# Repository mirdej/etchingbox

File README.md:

# AETZBOX
### DIY Mobile PCB Etching KIT

## The Idea 
Build a portable / mobile PCB etching workstation that fulfills these criteria
* waterproof
* able to etch 100x160mm double sided boards with 8mil precision
* low cost.  total bill of materials should not exceed 150 CHF
* diy approach, mostly laser cut plexi and easily sourceable materials
* fits in a RAKO Box

Some guiding ideas
* use very little but always fresh chemicals 
* good heat management: etching has to be done at 45-50 degrees celsius, developer has to be kept at >20 degrees as well (in my workshop, temperatures can easily drop below 16 degrees and developing is a pain).
* all material and chemicals travel in the box. liquid waste can travel in the box as well until it can properly disposed of.
* should be easy to clean. no electronics exposed to moisture. 
* as few as possible switches and electrical contacts exposed to the harsh etching environment
* self illuminating

## More Info
https://wiki.sgmk-ssam.ch/index.php/EtchingBox

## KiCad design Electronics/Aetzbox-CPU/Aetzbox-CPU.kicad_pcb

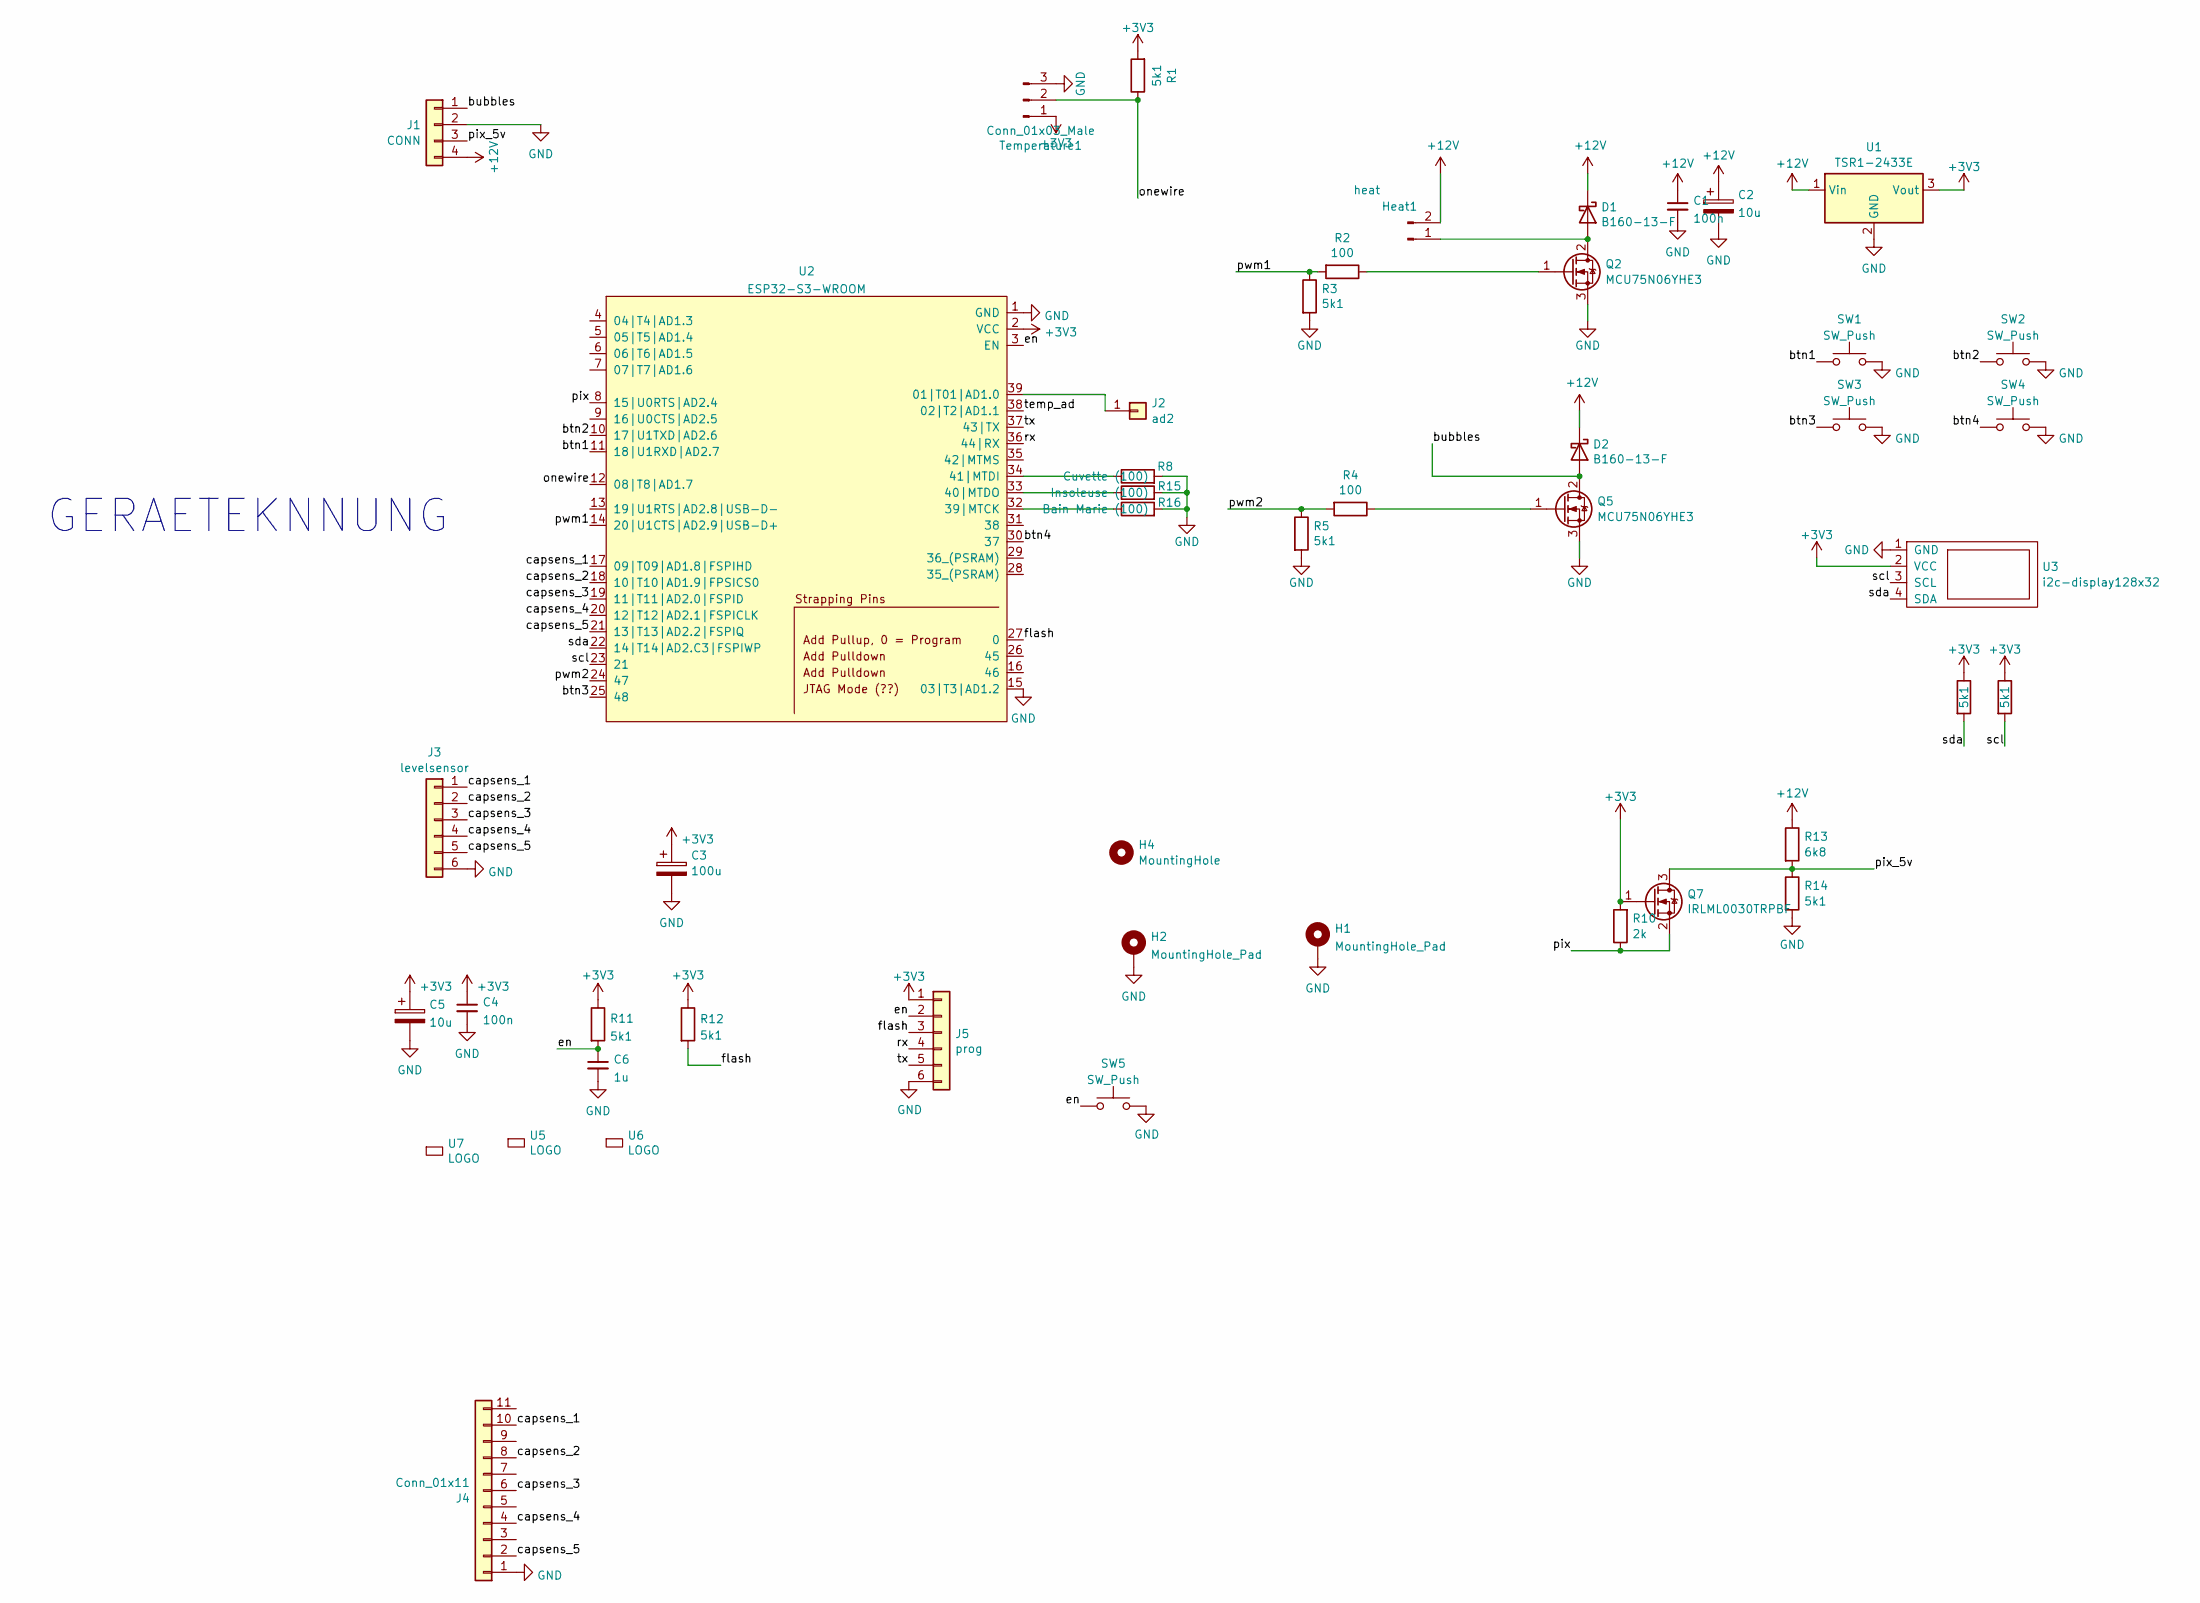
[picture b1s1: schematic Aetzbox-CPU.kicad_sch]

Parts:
C1, C4: 100n; C_0603_1608Metric_Pad1.05x0.95mm_HandSolder
C2, C5: 10u; C_1206_3216Metric_Pad1.42x1.75mm_HandSolder
C3: 100u; CP_EIA-6032-20_AVX-F
C6: 1u; C_0603_1608Metric_Pad1.05x0.95mm_HandSolder
D1, D2: B160-13-F; D_SMA-SMB_Universal_Handsoldering
H1, H2: MountingHole_Pad; MountingHole_2.5mm_Pad
H4: MountingHole; MountingHole_2.5mm
Heat1: heat; Molex_Mini-Fit_Jr_5566-02A_2x01_P4.20mm_Vertical
J1: CONN; Molex_Mini-Fit_Jr_5569-04A2_2x02_P4.20mm_H+V
J2: ad2; Solderpad_1mm
J3: levelsensor; PinSocket_1x06_P1.27mm_Vertical
J4: Conn_01x11; Molex_200528-0100_1x10-1MP_P1.00mm_Horizontal
J5: prog; ESP-POGO-PROG-THT
Q2, Q5: MCU75N06YHE3; TO-252-2
Q7: IRLML0030TRPBF; SOT-23
R1, R3, R5, R6, R7, R11, R12, R14: 5k1; R_0805_2012Metric
R2, R4: 100; R_0805_2012Metric
R8: Cuvette (100); R_0805_2012Metric
R10: 2k; R_0805_2012Metric
R13: 6k8; R_0805_2012Metric
R15: Insoleuse (100); R_0805_2012Metric
R16: Bain Marie (100); R_0805_2012Metric
SW1, SW2, SW3, SW4: SW_Push; Alps_Tactile_Switch
SW5: SW_Push; MiniButtonPLCC4
Temperature1: Conn_01x03_Male; Molex_KK-254_AE-6410-03A_1x03_P2.54mm_Vertical
U1: TSR1-2433E; Converter_DCDC_TRACO_TSR1-xxxxE_THT
U2: ESP32-S3-WROOM
U3: i2c-display128x32; Bangood_I2C_Display
U5: LOGO; logo_anyma_tiny
U6: LOGO; logo_sgmk
U7: LOGO; OSHW-Logo2_7.3x6mm_SilkScreen

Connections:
+3V3: C3.1, C4.1, C5.1, J5.1, Q7.1 (G), R1.2, R6.1, R7.1, R10.2, R11.1, R12.1, Temperature1.1, U1.3 (Vout), U2.2 (VCC), U3.2 (VCC)
+12V: C1.1, C2.1, D1.1 (K), D2.1 (K), Heat1.2, J1.4, R13.1, U1.1 (Vin)
/btn1: SW1.1, U2.11 (18|U1RXD|AD2.7)
/btn2: SW2.1, U2.10 (17|U1TXD|AD2.6)
/btn3: SW3.1, U2.25 (48)
/btn4: SW4.1, U2.30 (37)
/bubbles: D2.2 (A), J1.1, Q5.2 (D)
/capsens_1: J3.1, J4.10, U2.17 (09|T09|AD1.8|FSPIHD)
/capsens_2: J3.2, J4.8, U2.18 (10|T10|AD1.9|FPSICS0)
/capsens_3: J3.3, J4.6, U2.19 (11|T11|AD2.0|FSPID)
/capsens_4: J3.4, J4.4, U2.20 (12|T12|AD2.1|FSPICLK)
/capsens_5: J3.5, J4.2, U2.21 (13|T13|AD2.2|FSPIQ)
/en: C6.1, J5.2, R11.2, SW5.2, U2.3 (EN)
/flash: J5.3, R12.2, U2.27 (0)
/onewire: R1.1, Temperature1.2, U2.12 (08|T8|AD1.7)
/pix: Q7.2 (S), R10.1, U2.8 (15|U0RTS|AD2.4)
/pix_5v: J1.3, Q7.3 (D), R13.2, R14.1
/pwm1: R2.2, R3.1, U2.14 (20|U1CTS|AD2.9|USB-D+)
/pwm2: R4.2, R5.1, U2.24 (47)
/rx: J5.4, U2.36 (44|RX)
/scl: R7.2, U2.23 (21), U3.3 (SCL)
/sda: R6.2, U2.22 (14|T14|AD2.C3|FSPIWP), U3.4 (SDA)
/temp_ad: U2.38 (02|T2|AD1.1)
/tx: J5.5, U2.37 (43|TX)
GND: C1.2, C2.2, C3.2, C4.2, C5.2, C6.2, H1.1, H2.1, J1.2, J3.6, J4.1, J5.6, Q2.3 (S), Q5.3 (S), R3.2, R5.2, R8.2, R14.2, R15.2, R16.2, SW1.2, SW2.2, SW3.2, SW4.2, SW5.1, Temperature1.3, U1.2 (GND), U2.1 (GND), U2.15 (03|T3|AD1.2), U2.40 (GND), U2.41 (GND), U3.1 (GND)
unnamed: D1.2 (A), Heat1.1, Q2.2 (D)
unnamed: J2.1, U2.39 (01|T01|AD1.0)
unnamed: Q2.1 (G), R2.1
unnamed: Q5.1 (G), R4.1
unnamed: R16.1, U2.32 (39|MTCK)
unnamed: R15.1, U2.33 (40|MTDO)
unnamed: R8.1, U2.34 (41|MTDI)

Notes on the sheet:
GERAETEKNNUNG

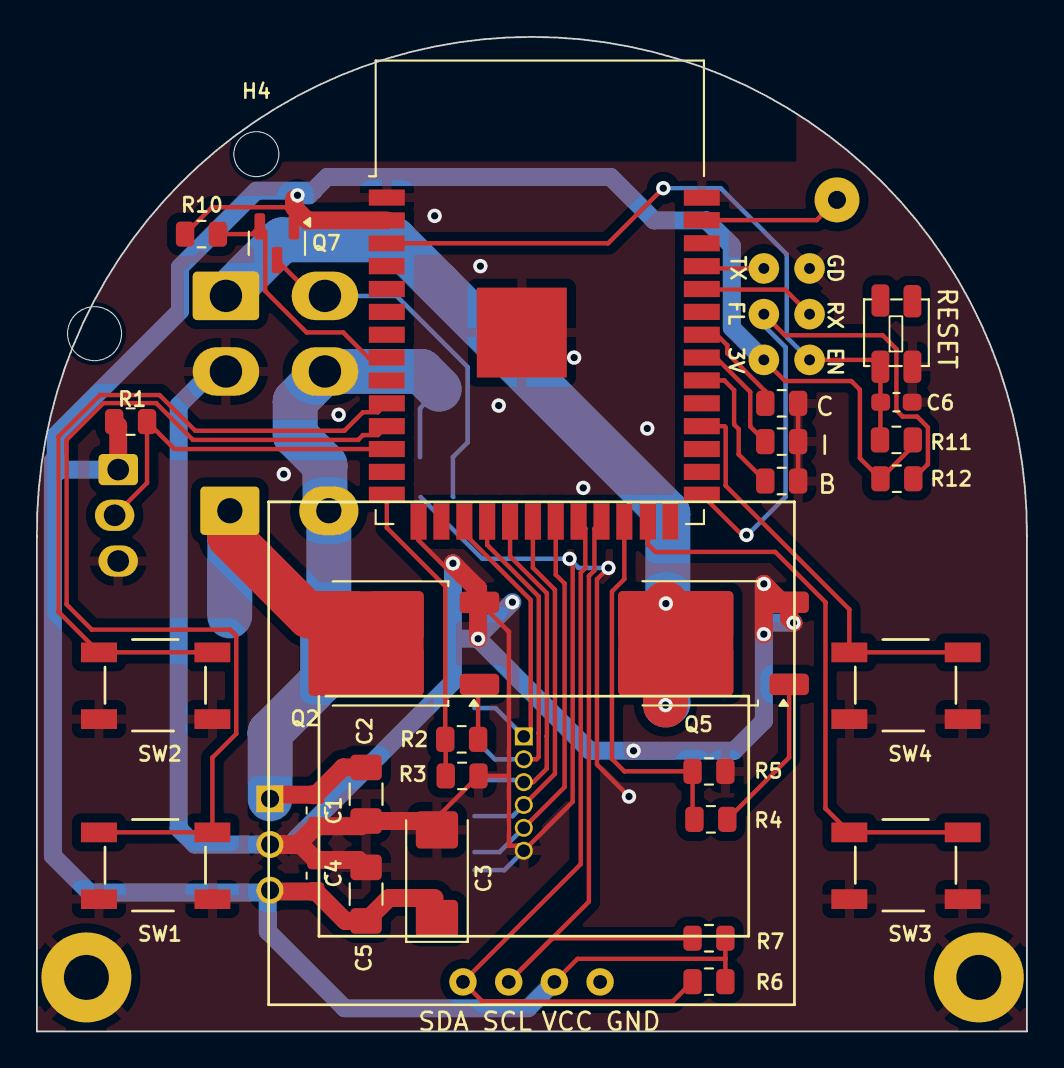
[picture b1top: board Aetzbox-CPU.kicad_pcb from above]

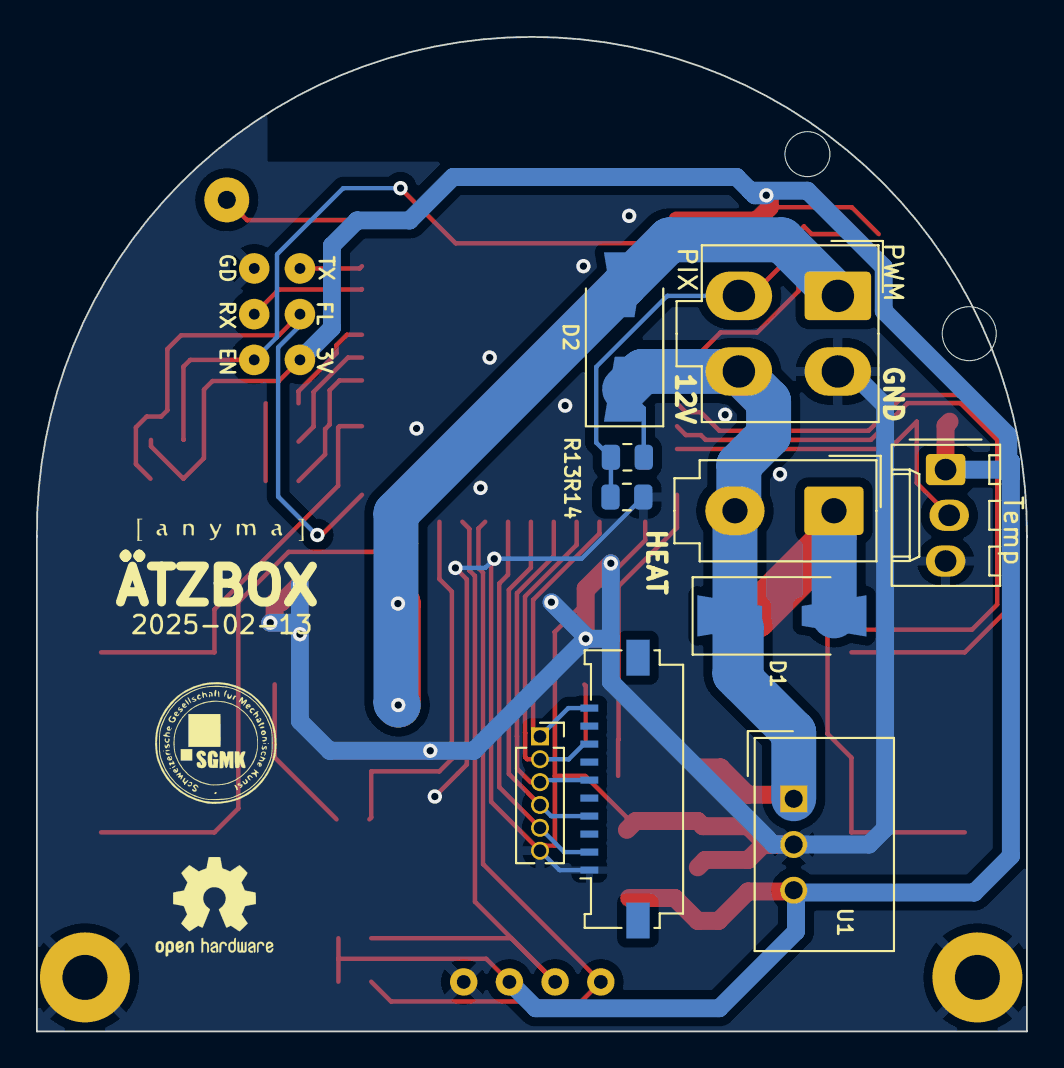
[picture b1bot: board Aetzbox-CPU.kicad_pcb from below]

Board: 2 copper layers, 55.0 x 55.3 mm, 47 parts (14 on the bottom side), 31 nets.

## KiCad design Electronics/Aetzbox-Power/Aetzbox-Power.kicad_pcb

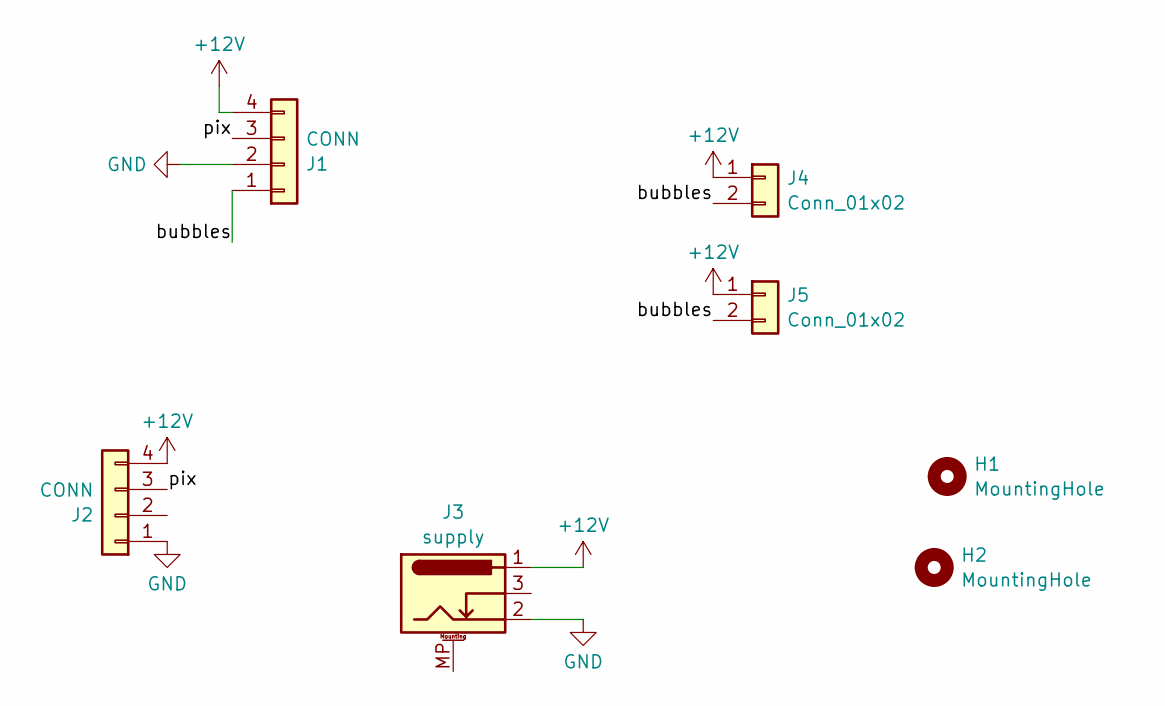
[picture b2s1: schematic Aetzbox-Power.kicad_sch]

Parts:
H1, H2: MountingHole; MountingHole_3.2mm_M3_DIN965
J1: CONN; Molex_Mini-Fit_Jr_5569-04A2_2x02_P4.20mm_H+V
J2: CONN; PinHeader_1x04_P2.54mm_Horizontal
J3: supply; BarrelJack_CUI_PJ-079BH_Horizontal
J4, J5: Conn_01x02; PinHeader_1x02_P2.54mm_Horizontal

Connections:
+12V: J1.4, J2.4, J3.1, J4.1, J5.1
/bubbles: J1.1, J4.2, J5.2
/pix: J1.3, J2.3
GND: J1.2, J2.1, J3.2

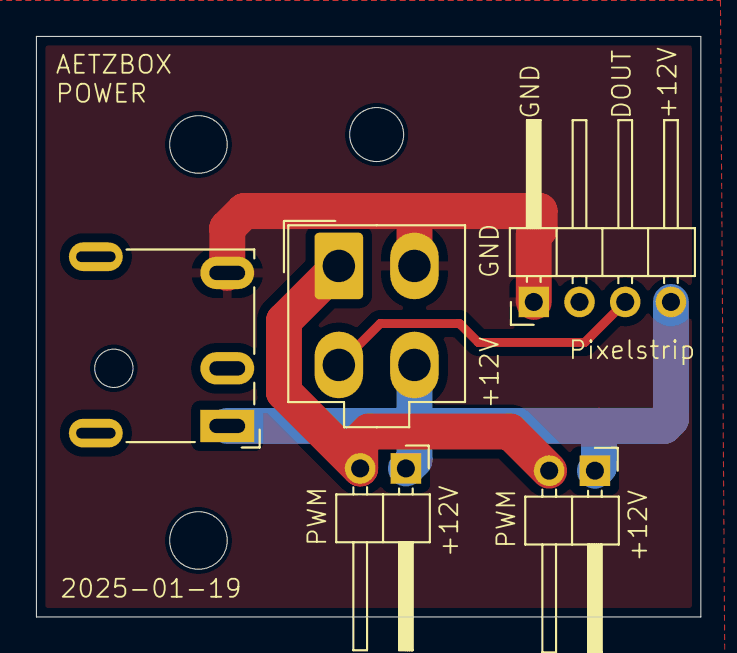
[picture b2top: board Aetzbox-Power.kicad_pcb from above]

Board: 2 copper layers, 36.9 x 32.2 mm, 7 parts (0 on the bottom side), 4 nets.

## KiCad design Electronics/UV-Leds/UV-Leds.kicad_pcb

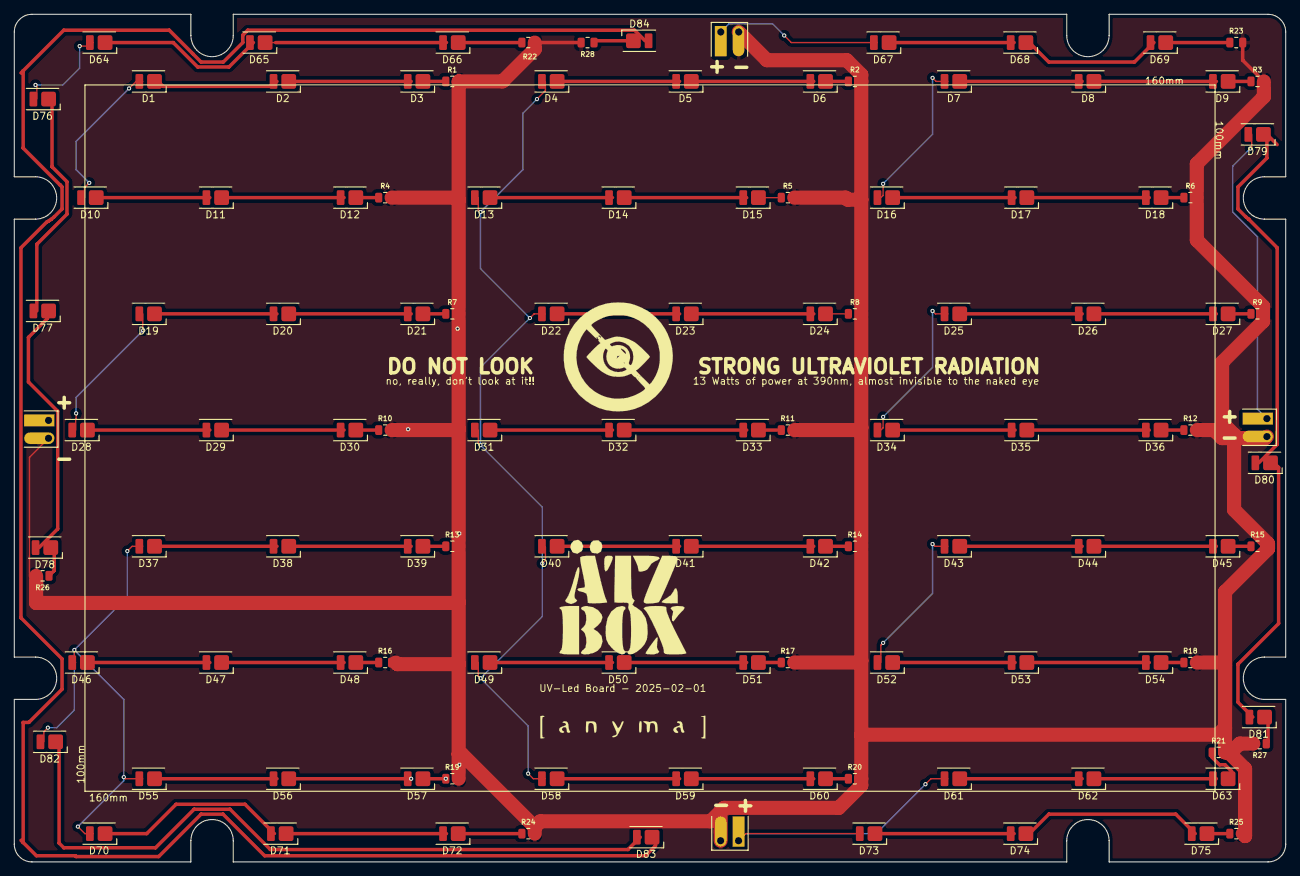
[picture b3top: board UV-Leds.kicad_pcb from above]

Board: 2 copper layers, 180.0 x 120.0 mm, 119 parts (0 on the bottom side), 86 nets.

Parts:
D1, D2, D3, D4, D5, D6, D7, D8, D9, D10, D11, D12, D13, D14, D15, D16, D17, D18, D19, D20, D21, D22, D23, D24, D25, D26, D27, D28, D29, D30, D31, D32, D33, D34, D35, D36, D37, D38, D39, D40, D41, D42, D43, D44, D45, D46, D47, D48, D49, D50, D51, D52, D53, D54, D55, D56, D57, D58, D59, D60, D61, D62, D63, D64, D65, D66, D67, D68, D69, D70, D71, D72, D73, D74, D75, D76, D77, D78, D79, D80, D81, D82, D83, D84: LED; LED_2835_UV-S2-2835UVTA-0.2W
J1, J2, J3, J4: Conn_01x02; ComboPinhead_02
R1, R2, R3, R4, R5, R6, R7, R8, R9, R10, R11, R12, R13, R14, R15, R16, R17, R18, R19, R20, R21, R22, R23, R24, R25, R26, R27, R28: R; R_0805_2012Metric
U1: LOGO; logo_aetz_box
U2: LOGO; logo_dontt_look
U3: LOGO; logo_anyma

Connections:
+12V: D1.2 (A), D4.2 (A), D7.2 (A), D10.2 (A), D13.2 (A), D16.2 (A), D19.2 (A), D22.2 (A), D25.2 (A), D28.2 (A), D31.2 (A), D34.2 (A), D37.2 (A), D40.2 (A), D43.2 (A), D46.2 (A), D49.2 (A), D52.2 (A), D55.2 (A), D58.2 (A), D61.2 (A), D64.2 (A), D67.2 (A), D70.2 (A), D73.2 (A), D76.2 (A), D79.2 (A), D82.2 (A), J1.1, J2.1, J3.1, J4.1
GND: J1.2, J2.2, J3.2, J4.2, R1.2, R2.2, R3.2, R4.2, R5.2, R6.2, R7.2, R8.2, R9.2, R10.2, R11.2, R12.2, R13.2, R14.2, R15.2, R16.2, R17.2, R18.2, R19.2, R20.2, R21.2, R22.2, R23.2, R24.2, R25.2, R26.2, R27.2, R28.2
unnamed: D1.1 (K), D2.2 (A)
unnamed: D2.1 (K), D3.2 (A)
unnamed: D3.1 (K), R1.1
unnamed: D4.1 (K), D5.2 (A)
unnamed: D5.1 (K), D6.2 (A)
unnamed: D6.1 (K), R2.1
unnamed: D7.1 (K), D8.2 (A)
unnamed: D8.1 (K), D9.2 (A)
unnamed: D9.1 (K), R3.1
unnamed: D10.1 (K), D11.2 (A)
unnamed: D11.1 (K), D12.2 (A)
unnamed: D12.1 (K), R4.1
unnamed: D13.1 (K), D14.2 (A)
unnamed: D14.1 (K), D15.2 (A)
unnamed: D15.1 (K), R5.1
unnamed: D16.1 (K), D17.2 (A)
unnamed: D17.1 (K), D18.2 (A)
unnamed: D18.1 (K), R6.1
unnamed: D19.1 (K), D20.2 (A)
unnamed: D20.1 (K), D21.2 (A)
unnamed: D21.1 (K), R7.1
unnamed: D22.1 (K), D23.2 (A)
unnamed: D23.1 (K), D24.2 (A)
unnamed: D24.1 (K), R8.1
unnamed: D25.1 (K), D26.2 (A)
unnamed: D26.1 (K), D27.2 (A)
unnamed: D27.1 (K), R9.1
unnamed: D28.1 (K), D29.2 (A)
unnamed: D29.1 (K), D30.2 (A)
unnamed: D30.1 (K), R10.1
unnamed: D31.1 (K), D32.2 (A)
unnamed: D32.1 (K), D33.2 (A)
unnamed: D33.1 (K), R11.1
unnamed: D34.1 (K), D35.2 (A)
unnamed: D35.1 (K), D36.2 (A)
unnamed: D36.1 (K), R12.1
unnamed: D37.1 (K), D38.2 (A)
unnamed: D38.1 (K), D39.2 (A)
unnamed: D39.1 (K), R13.1
unnamed: D40.1 (K), D41.2 (A)
unnamed: D41.1 (K), D42.2 (A)
unnamed: D42.1 (K), R14.1
unnamed: D43.1 (K), D44.2 (A)
unnamed: D44.1 (K), D45.2 (A)
unnamed: D45.1 (K), R15.1
unnamed: D46.1 (K), D47.2 (A)
unnamed: D47.1 (K), D48.2 (A)
unnamed: D48.1 (K), R16.1
unnamed: D49.1 (K), D50.2 (A)
unnamed: D50.1 (K), D51.2 (A)
unnamed: D51.1 (K), R17.1
unnamed: D52.1 (K), D53.2 (A)
unnamed: D53.1 (K), D54.2 (A)
unnamed: D54.1 (K), R18.1
unnamed: D55.1 (K), D56.2 (A)
unnamed: D56.1 (K), D57.2 (A)
unnamed: D57.1 (K), R19.1
unnamed: D58.1 (K), D59.2 (A)
unnamed: D59.1 (K), D60.2 (A)
unnamed: D60.1 (K), R20.1
unnamed: D61.1 (K), D62.2 (A)
unnamed: D62.1 (K), D63.2 (A)
unnamed: D63.1 (K), R21.1
unnamed: D64.1 (K), D65.2 (A)
unnamed: D65.1 (K), D66.2 (A)
unnamed: D66.1 (K), R22.1
unnamed: D67.1 (K), D68.2 (A)
unnamed: D68.1 (K), D69.2 (A)
unnamed: D69.1 (K), R23.1
unnamed: D70.1 (K), D71.2 (A)
unnamed: D71.1 (K), D72.2 (A)
unnamed: D72.1 (K), R24.1
unnamed: D73.1 (K), D74.2 (A)
unnamed: D74.1 (K), D75.2 (A)
unnamed: D75.1 (K), R25.1
unnamed: D76.1 (K), D77.2 (A)
unnamed: D77.1 (K), D78.2 (A)
unnamed: D78.1 (K), R26.1
unnamed: D79.1 (K), D80.2 (A)
unnamed: D80.1 (K), D81.2 (A)
unnamed: D81.1 (K), R27.1
unnamed: D82.1 (K), D83.2 (A)
unnamed: D83.1 (K), D84.2 (A)
unnamed: D84.1 (K), R28.1

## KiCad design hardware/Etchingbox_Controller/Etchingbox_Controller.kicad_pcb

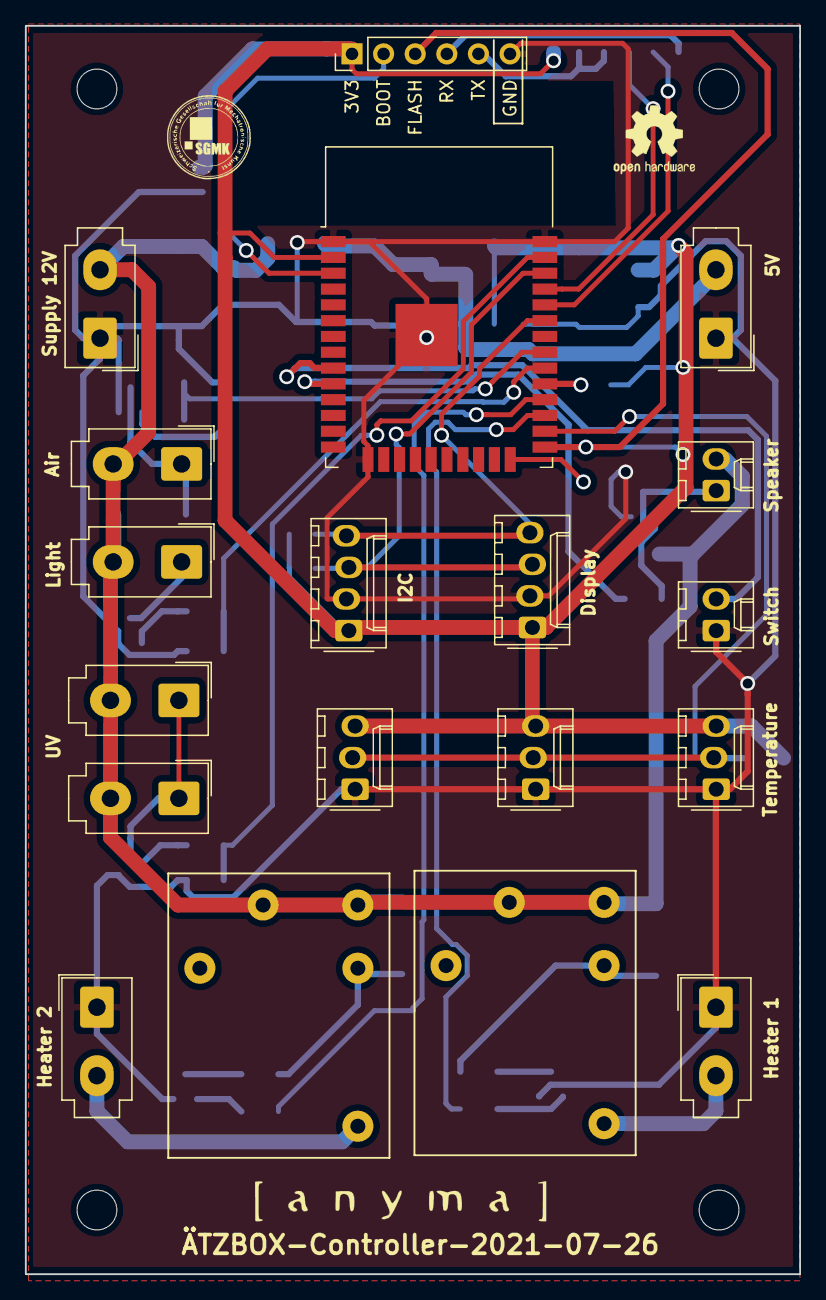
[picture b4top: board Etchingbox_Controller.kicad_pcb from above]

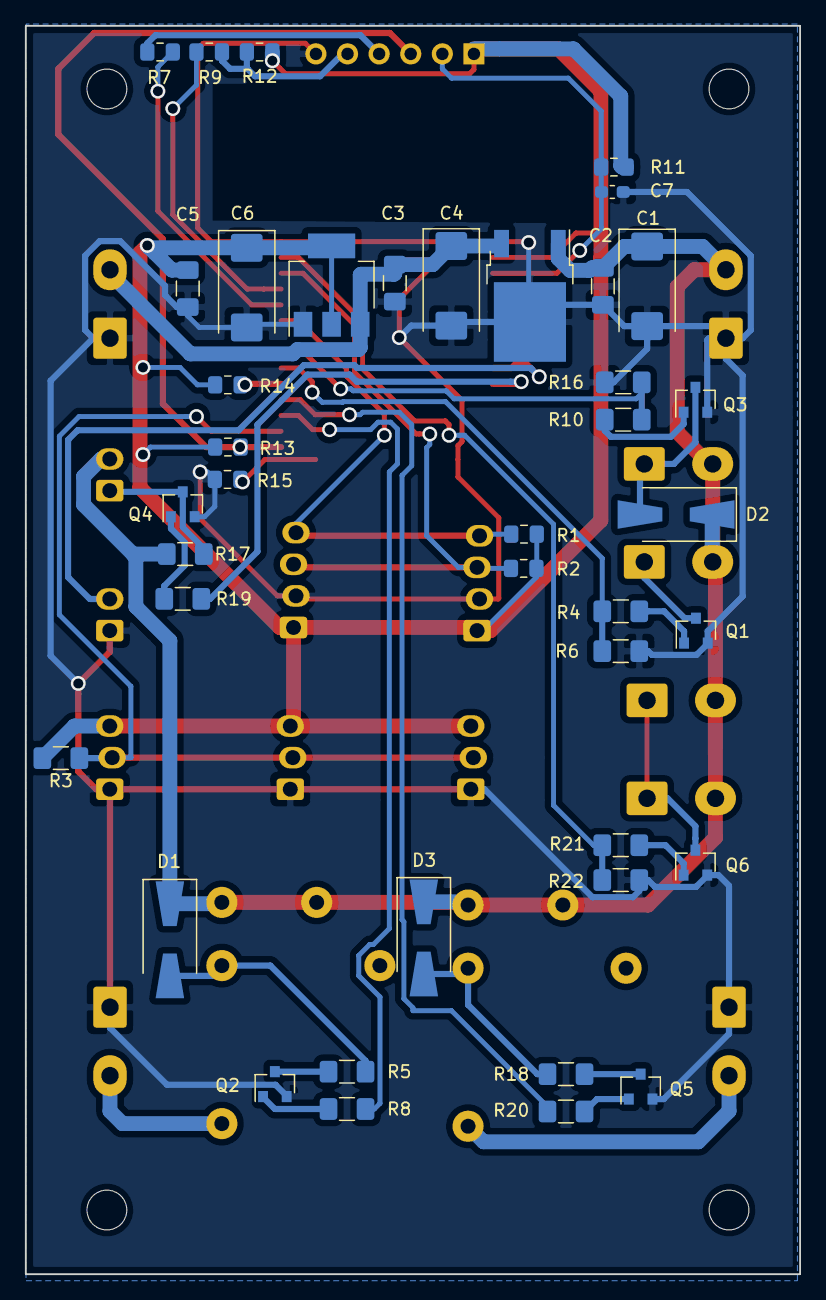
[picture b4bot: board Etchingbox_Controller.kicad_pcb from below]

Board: 2 copper layers, 62.2 x 100.3 mm, 66 parts (40 on the bottom side), 38 nets.

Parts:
Bubbles1: Conn_01x02_Male; Molex_Mini-Fit_Jr_5566-02A_2x01_P4.20mm_Vertical
C1, C4, C6: CP; CP_EIA-7343-20_Kemet-V_Pad2.25x2.55mm_HandSolder
C2, C3, C5: 100n; C_1206_3216Metric_Pad1.42x1.75mm_HandSolder
C7: 1u; C_0603_1608Metric_Pad1.05x0.95mm_HandSolder
D1, D3: D_Schottky; D_SMA-SMB_Universal_Handsoldering
D2: B160-13-F; D_SMA-SMB_Universal_Handsoldering
Display1: Conn_01x04_Male; Molex_KK-254_AE-6410-04A_1x04_P2.54mm_Vertical
H1, H2, H3, H4: MountingHole; MountingHole_3.2mm_M3_DIN965
Heater1, Heater2: Conn_01x02_Male; Molex_Mini-Fit_Jr_5566-02A_2x01_P4.20mm_Vertical
I2C1: Conn_01x04_Male; Molex_KK-254_AE-6410-04A_1x04_P2.54mm_Vertical
J1: Conn_01x06; PinHeader_1x06_P2.54mm_Vertical
K1, K2: LZ_9H; LZ-9H
Lightpad1: Conn_01x02_Male; Molex_Mini-Fit_Jr_5566-02A_2x01_P4.20mm_Vertical
Piezo1: Conn_01x02_Male; Molex_KK-254_AE-6410-02A_1x02_P2.54mm_Vertical
Q1, Q3, Q6: IRLML2502PBF; SOT-23
Q2, Q4, Q5: BC847; SOT-23
R1, R2, R11, R12, R13, R14, R15: 10k; R_0805_2012Metric_Pad1.15x1.40mm_HandSolder
R3: 4k7; R_1206_3216Metric_Pad1.42x1.75mm_HandSolder
R4, R10, R21: 100; R_1206_3216Metric_Pad1.42x1.75mm_HandSolder
R5, R18: 150; R_1206_3216Metric_Pad1.42x1.75mm_HandSolder
R6, R16, R22: 10k; R_1206_3216Metric_Pad1.42x1.75mm_HandSolder
R7, R9: 1k; C_0805_2012Metric_Pad1.15x1.40mm_HandSolder
R8, R20: 300; R_1206_3216Metric_Pad1.42x1.75mm_HandSolder
R17, R19: 1k; R_1206_3216Metric_Pad1.42x1.75mm_HandSolder
Supply1, Supply2: Conn_01x02_Male; Molex_Mini-Fit_Jr_5566-02A_2x01_P4.20mm_Vertical
Switch1: Conn_01x02_Male; Molex_KK-254_AE-6410-02A_1x02_P2.54mm_Vertical
Temperature1, Temperature2, Temperature3: Conn_01x03_Male; Molex_KK-254_AE-6410-03A_1x03_P2.54mm_Vertical
U1: L7805; TO-252-2
U2: LD1117S33TR_SOT223; SOT-223-3_TabPin2
U3: ESP32-WROOM; ESP32-WROOM-32
U4: LOGO; logo_anyma
U5: LOGO; logo_sgmk
U6: LOGO; OSHW-Logo2_7.3x6mm_SilkScreen
UV1, UV2: Conn_01x02_Male; Molex_Mini-Fit_Jr_5566-02A_2x01_P4.20mm_Vertical

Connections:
+3V3: C5.1, C6.1, Display1.1, I2C1.1, J1.1, R1.1, R2.1, R3.2, R11.1, R12.1, R13.1, R14.1, Temperature1.3, Temperature2.3, Temperature3.3, U2.2, U3.2
+5V: C3.1, C4.1, Supply2.2, U1.3, U2.3
+12V: Bubbles1.2, C1.1, C2.1, D1.1, D2.1, D3.1, K1.3, K1.4, K2.3, K2.4, Lightpad1.2, Piezo1.2, R17.2, Supply1.2, U1.1, UV1.2, UV2.2
/SCL: Display1.3, I2C1.3, R2.2, U3.36
/SDA: Display1.4, I2C1.4, R1.2, U3.33
/bubbles: R10.2, R16.1, U3.31
/cs: R14.2, U3.29
/en: C7.1, J1.2, R11.2, U3.3
/gpio0: J1.3, R13.2, U3.25
/heat_1: R8.2, U3.27
/heat_2: R20.2, U3.28
/led: R15.1, U3.24
/light: R4.2, R6.1, U3.30
/rx: J1.4, R7.2
/sensors: R3.1, Temperature1.2, Temperature2.2, Temperature3.2, U3.26
/sound: R19.2, U3.10
/switch: Switch1.2, U3.9
/tx: J1.5, R9.2, R12.2
/uv: R21.2, R22.1, U3.37
GND: C1.2, C2.2, C3.2, C4.2, C5.2, C6.2, C7.2, Display1.2, Heater1.1, Heater2.1, I2C1.2, J1.6, Q1.2, Q2.2, Q3.2, Q4.2, Q5.2, Q6.2, R6.2, R15.2, R16.2, R22.2, Supply1.1, Supply2.1, Switch1.1, Temperature1.1, Temperature2.1, Temperature3.1, U1.2, U2.1, U3.1, U3.15, U3.38, U3.39
unnamed: Bubbles1.1, D2.2, Q3.3
unnamed: D1.2, K1.2, R5.2
unnamed: D3.2, K2.2, R18.2
unnamed: Heater1.2, K1.1
unnamed: Heater2.2, K2.1
unnamed: Lightpad1.1, Q1.3
unnamed: Piezo1.1, Q4.3, R17.1
unnamed: Q1.1, R4.1
unnamed: Q2.1, R8.1
unnamed: Q2.3, R5.1
unnamed: Q3.1, R10.1
unnamed: Q4.1, R19.1
unnamed: Q5.1, R20.1
unnamed: Q5.3, R18.1
unnamed: Q6.1, R21.1
unnamed: Q6.3, UV1.1, UV2.1
unnamed: R7.1, U3.34
unnamed: R9.1, U3.35

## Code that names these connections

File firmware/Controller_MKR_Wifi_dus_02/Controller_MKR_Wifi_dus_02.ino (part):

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#define PIN_RELAY_HEAT 	4
#define PIN_RELAY_HEAT_2 	5
#define PIN_UV 				3
#define	PIN_LIGHT			1
#define	PIN_BUBBLES			2
#define PIN_SWITCH			7
#define	PIN_PIEZO			0
#define PIN_ONE_WIRE_BUS 	6

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
//-------------------------------- Globals

OneWire 						oneWire(PIN_ONE_WIRE_BUS);
DallasTemperature 				temperature_sensors(&oneWire);
DeviceAddress 					acid_temperature_sensor_address = ACID_TEMPERATURE_SENSOR_ADDRESS;
DeviceAddress					ambient_temperature_sensor_address = AMBIENT_TEMPERATURE_SENSOR_ADDRESS;
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	pinMode(PIN_RELAY_HEAT, 	OUTPUT);			
	pinMode(PIN_RELAY_HEAT_2, 	OUTPUT);			
	pinMode(PIN_UV, 			OUTPUT);			
	pinMode(PIN_LIGHT, 			OUTPUT);			
	pinMode(PIN_BUBBLES,	 	OUTPUT);			
	pinMode(PIN_PIEZO, 			OUTPUT);			
	pinMode(PIN_SWITCH, 		INPUT_PULLUP);			

	Serial.begin(9600);			
	tone(PIN_PIEZO,800,100);
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		u8g2.sendBuffer();

		for(i = 0; i < 255; i++) {
			analogWrite(PIN_LIGHT,i);
			delay(1);
		}
		for(i = 255; i > 0; i--) {
			analogWrite(PIN_LIGHT,i);
			delay(1);
		}
		analogWrite(PIN_LIGHT,0);


		delay(500);
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		u8g2.print("Bubbles");
		u8g2.sendBuffer();
		for(i = 0; i < 255; i++) {
			analogWrite(PIN_BUBBLES,i);
			delay(1);
		}
		for(i = 255; i > 0; i--) {
			analogWrite(PIN_BUBBLES,i);
			delay(1);
		}
		analogWrite(PIN_BUBBLES,0);
		delay(500);
		tone(PIN_PIEZO,880,100);
	}
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
	while (wait) {
		if (millis() > wait_until) wait = false;
		if (digitalRead(PIN_SWITCH) == LOW)  wait = false;
	}

	tone(PIN_PIEZO,900,100);
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	digitalWrite(PIN_RELAY_HEAT, 		HIGH);			
	digitalWrite(PIN_RELAY_HEAT_2, 	HIGH);			
	digitalWrite(PIN_UV, 				HIGH);			
	digitalWrite(PIN_LIGHT, 			HIGH);			
	digitalWrite(PIN_BUBBLES,	 		HIGH);			

}

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
void check_button() {	
	static char old_state;
	char state = digitalRead(PIN_SWITCH);
	if (state == old_state) return;
	old_state = state;
	if (state) return;
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void check_ramps() {	
	if (lighpad_power < lighpad_target_power) lighpad_power++;
	if (lighpad_power > lighpad_target_power) lighpad_power--;
	analogWrite(PIN_LIGHT, lighpad_power);

	//if (uv_power < uv_target_power) uv_power++;
  if (uv_power < uv_target_power){ 
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
	if (bubble_power < bubble_target_power) bubble_power++;
	if (bubble_power > bubble_target_power) bubble_power--;
	analogWrite(PIN_BUBBLES, bubble_power);
}
//----------------------------------------------------------------------------------------
//																		uv flashing done
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
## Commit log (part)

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2014-05-13 added readme
2014-05-13 redme
2014-05-13 added first version of controler pcb and firmware
2014-05-13 basic heater control
2018-11-13 make place for completely new version
2018-11-16 new approach
2018-11-16 change mosfets, smaller borad
2018-11-26 Basic fuctions
2018-11-26 add sketchup models
2018-11-29 new bubble unit, holes for china plugs
2018-11-30 new basin holder
2018-11-30 4mm smaller lightpad.
2018-11-30 correct uv height. lighter lid, text
2018-11-30 some corrections
2018-12-01 fix missing link
2018-12-02 small corrections to holes. logo
2018-12-02 forgot to add logo.h
2018-12-03 pimped display
2018-12-03 workshop photos
2018-12-04 some minor hardware corrections during workshop. seperate logos. merge display code by dusjagr. add ambient temperatur display
2018-12-04 add lid holder
2019-01-21 full stop uv when finished flashing. no ramp down
2019-02-08 add more sounds, temperature log option, safety check
2019-02-08 try pulsing airpump
2019-02-08 Using SAMD Timer 4 as slow PWM (crude way) to prevent whining of air pump
2019-02-09 add bath temperture rise safety checks
2019-02-11 prevent slow heat rate error when bath is warm)
2019-02-16 add new version of ub leds that should cover whole board
2021-07-26 stash latest version with MKR-Wifi before changing to ESP32
2021-07-26 esp3 version
2022-04-10 add esp32 firmware
2025-04-17 remove 2018 version
2025-04-17 2025 version hardware
2025-04-17 rm old firmware
2025-04-17 rm hardware 2018
2025-04-17 redme typos
2025-04-17 firmware version workshop april
2025-04-17 corret resistor value
2025-04-17 add bom for uv led boards
2025-04-17 add bom
2025-04-17 Add sketch
2025-04-17 Add dark image
2025-05-17 disable waterlevel sensor !!!
2025-08-05 add besteck

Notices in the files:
firmware/Controller_MKR_Wifi_dus_02/Controller_MKR_Wifi_dus_02.ino:
Copyright:	2018 Michael Egger, me@anyma.ch
License: 	This is FREE software (as in free speech, not necessarily free beer)
published under gnu GPL v.3
